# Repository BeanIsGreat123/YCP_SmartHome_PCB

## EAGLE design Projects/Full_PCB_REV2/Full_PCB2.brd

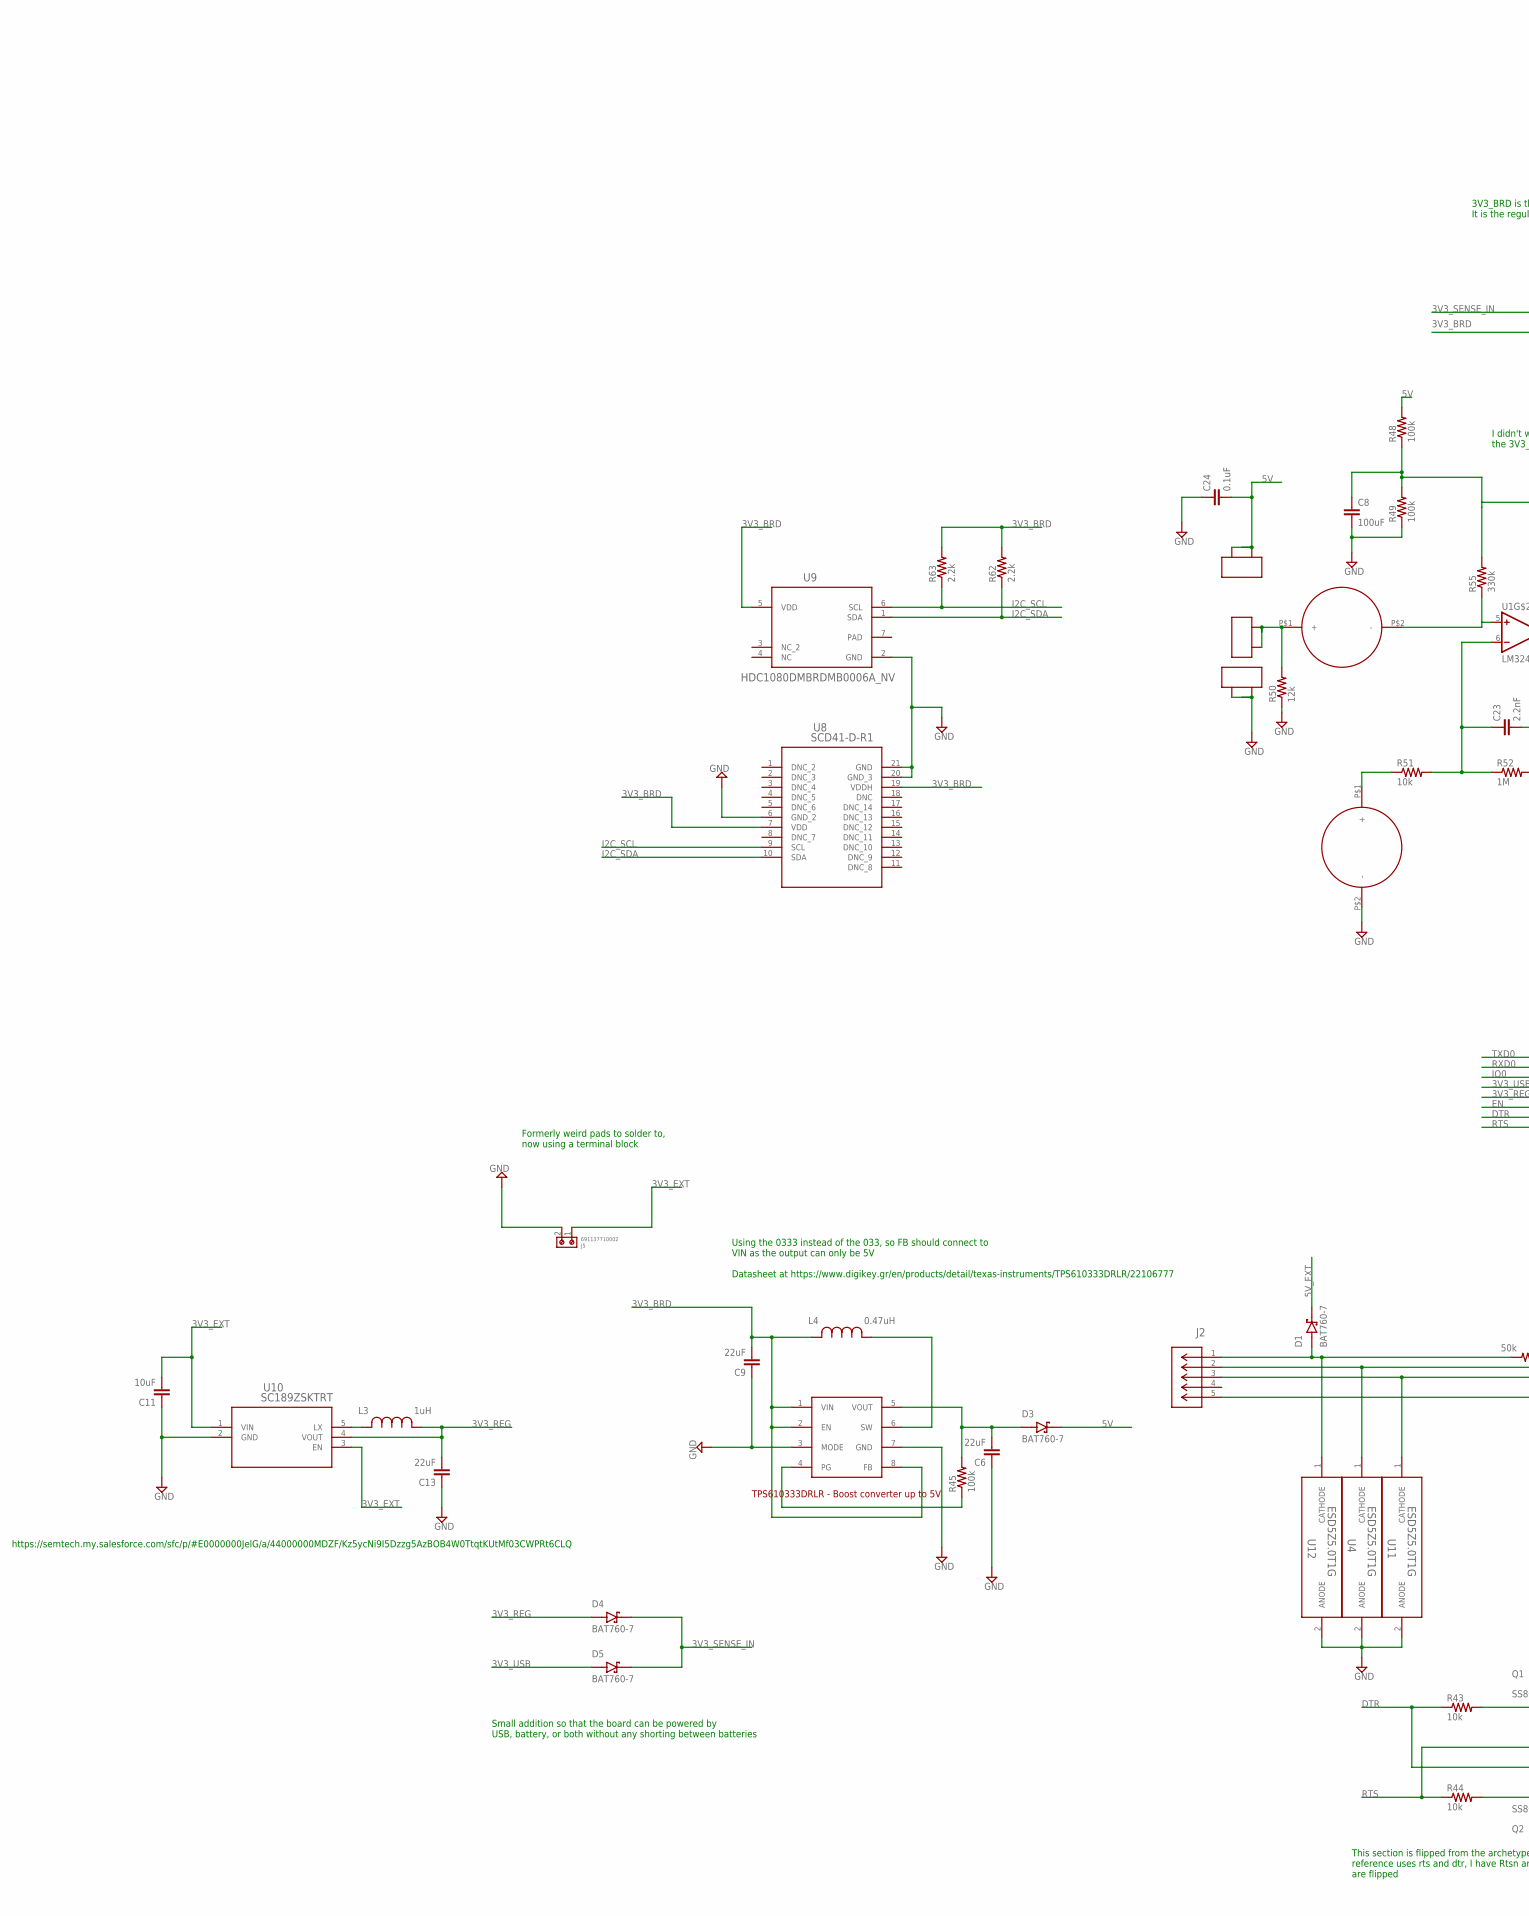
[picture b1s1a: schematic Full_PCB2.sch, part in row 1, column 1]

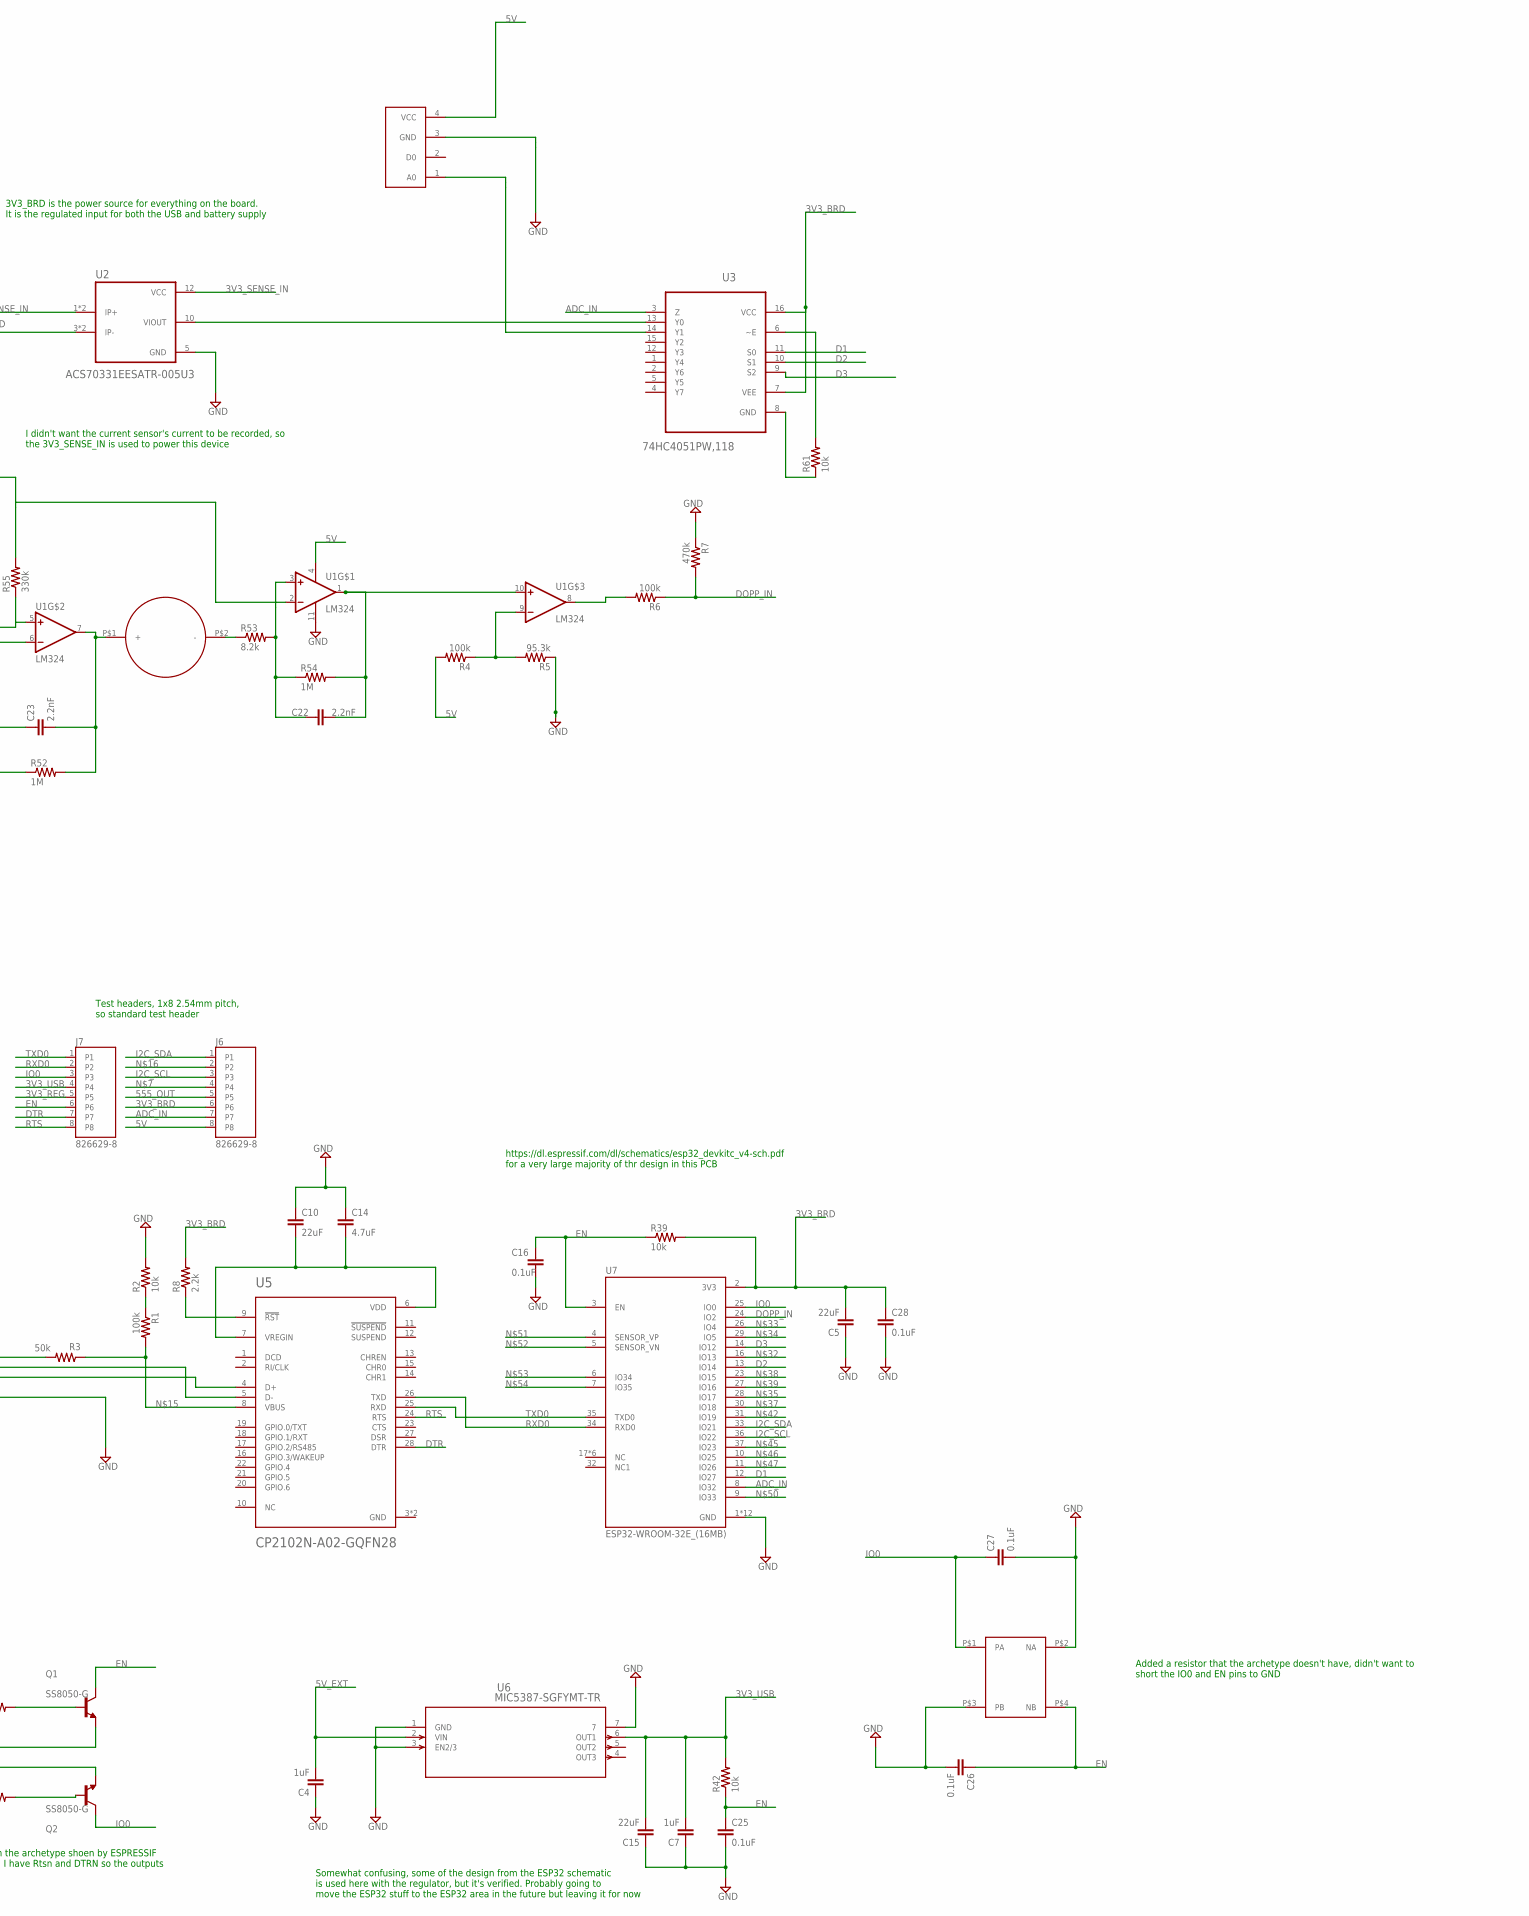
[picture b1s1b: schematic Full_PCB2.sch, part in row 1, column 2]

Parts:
C4, C7: 1uF; C0603
C5, C6, C9, C13, C15: 22uF; C0603
C8: 100uF; C1206
C10: 22uF; C0805
C11: 10uF; C0603
C14: 4.7uF; C0402
C16, C24, C25, C26, C27, C28: 0.1uF; C0402
C22, C23: 2.2nF; C0402
D1, D3, D4, D5: BAT760-7; SOD2513X120N
J2: 10118193-0001LF; CONN_10118193-0001LF_AMP
J5: 691137710002
J6, J7: 826629-8; TE_826629-8
L3: 1uH; DFE252012P-1R0M=P2
L4: 0.47uH; DFE252012P-1R0M=P2
Q1, Q2: SS8050-G; TRANS_SS8050-G
R1, R4, R6, R45, R48, R49: 100k; R0402
R2, R39, R42, R43, R44, R51, R61: 10k; R0402
R3: 50k; R0402
R5: 95.3k; R0402
R7: 470k; R0402
R8, R62, R63: 2.2k; R0402
R50: 12k; R0402
R52, R54: 1M; R0402
R53: 8.2k; R0402
R55: 330k; R0402
U1: LM324; SOIC127P600X175-14N
U2: ACS70331EESATR-005U3; ALLEGRO_ACS70331EESATR-005U3
U3: 74HC4051PW,118; SOP65P640X110-16N
U4, U11, U12: ESD5Z5.0T1G; SOD-523_0P9X1P3_ONS
U5: CP2102N-A02-GQFN28; QFN50P500X500X80-29N
U6: MIC5387-SGFYMT-TR; MLF-6_MT_MCH
U7: ESP32-WROOM-32E_(16MB); XCVR_ESP32-WROOM-32E_(16MB)
U8: SCD41-D-R1; SCD41-D-R1_SEN
U9: HDC1080DMBRDMB0006A_NV; DMB0006A_NV
U10: SC189ZSKTRT; SOT23-5-SC189_SEM
U14: TPS610333DRLR
U$1, U$2, U$5: 2PIN_HEADER
U$3: MQ_7; MQ-7
U$6: 219-2LPST
U$7, U$8, U$9: 865080540002

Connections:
3V3_BRD: C5.2, C9.2, C28.1, J6.6, L4.2, R8.2, R39.2, R62.2, R63.2, U2.3 (IP-), U2.4 (IP-), U3.7 (VEE), U3.16 (VCC), U7.2 (3V3), U8.7 (VDD), U8.19 (VDDH), U9.5 (VDD), U14.1 (VIN), U14.2 (EN), U14.8 (FB)
3V3_EXT: C11.2, J5.1, U10.1 (VIN), U10.3 (EN)
3V3_REG: C13.2, D4.A, J7.5, L3.1, U10.4 (VOUT)
3V3_SENSE_IN: D4.C (K), D5.C (K), U2.1 (IP+), U2.2 (IP+), U2.12 (VCC)
3V3_USB: C7.2, C15.2, D5.A, J7.4, R42.2, U6.6 (OUT1)
5V: C24.2, D3.C (K), J6.8, R4.2, R48.2, U1.4 (VCC+), U$2.1, U$2.2, U$3.4 (VCC)
5V1: C6.2, D3.A, R45.2, U14.5 (VOUT)
5V_EXT: C4.2, D1.C (K), U6.2 (VIN)
555_OUT: J6.5
ADC_IN: J6.7, U3.3 (Z), U7.8 (IO32)
D1: U3.11 (S0), U7.12 (IO27)
D2: U3.10 (S1), U7.13 (IO14)
D3: U3.9 (S2), U7.14 (IO12)
DOPP_IN: R6.1, R7.2, U7.24 (IO2)
DTR: J7.7, Q2.2 (E), R43.1, U5.28 (DTR)
EN: C16.1, C25.1, C26.1, J7.6, Q1.3 (C), R39.1, R42.1, U7.3 (EN), U$6.P$4 (NB)
GND: C4.1, C5.1, C6.1, C7.1, C8.2, C9.1, C10.1, C11.1, C13.1, C14.1, C15.1, C16.2, C24.1, C25.2, C26.2, C27.2, C28.2, J2.5, J5.2, R2.2, R5.1, R7.1, R49.1, R50.1, U1.11 (VCC-), U2.5 (GND), U4.2 (ANODE), U5.3 (GND), U5.29 (GND), U6.1 (GND), U6.3 (EN2/3), U6.7, U7.1 (GND), U7.15 (GND), U7.38 (GND), U7.39_1 (GND), U7.39_2 (GND), U7.39_3 (GND), U7.39_4 (GND), U7.39_5 (GND), U7.39_6 (GND), U7.39_7 (GND), U7.39_8 (GND), U7.39_9 (GND), U8.6 (GND_2), U8.20 (GND_3), U8.21 (GND), U9.2 (GND), U10.2 (GND), U11.2 (ANODE), U12.2 (ANODE), U14.3 (MODE), U14.7 (GND), U$3.3 (GND), U$5.1, U$5.2, U$6.P$2 (NA), U$6.P$3 (PB), U$7.P$2 (-)
I2C_SCL: J6.3, R63.1, U7.36 (IO22), U8.9 (SCL), U9.6 (SCL)
I2C_SDA: J6.1, R62.1, U7.33 (IO21), U8.10 (SDA), U9.1 (SDA)
IO0: C27.1, J7.3, Q2.3 (C), U7.25 (IO0), U$6.P$1 (PA)
unnamed: D1.A, J2.1, R3.2, U12.1 (CATHODE)
unnamed: R4.1, R5.2, U1.9 (INVERTING_INPUT3)
unnamed: C23.1, R51.2, R52.1, U1.6 (INVERTING_INPUT2)
unnamed: C23.2, R52.2, U1.7 (OUTPUT2), U$9.P$1 (+)
unnamed: R53.1, U$9.P$2 (-)
unnamed: C22.1, R53.2, R54.1, U1.3 (NON-INVERTING_INPUT1)
unnamed: J6.4, U2.10 (VIOUT), U3.13 (Y0)
unnamed: R6.2, U1.8 (OUTPUT3)
unnamed: R51.1, U$7.P$1 (+)
unnamed: R45.1, U14.4 (PG)
unnamed: C8.1, R48.1, R49.2, R55.2, U1.2 (INVERTING_INPUT1)
unnamed: J2.2, U4.1 (CATHODE), U5.5 (D-)
unnamed: J2.3, U5.4 (D+), U11.1 (CATHODE)
unnamed: R1.2, R3.1, U5.8 (VBUS)
unnamed: J6.2, U3.14 (Y1), U$3.1 (A0)
unnamed: R1.1, R2.1
unnamed: R8.1, U5.9 (!RST)
unnamed: R61.1, U3.8 (GND)
unnamed: R61.2, U3.6 (~E)
unnamed: C10.2, C14.2, U5.6 (VDD), U5.7 (VREGIN)
unnamed: Q1.1 (B), R43.2
unnamed: Q2.1 (B), R44.2
unnamed: R50.2, U$1.1, U$1.2, U$8.P$1 (+)
unnamed: L3.2, U10.5 (LX)
unnamed: L4.1, U14.6 (SW)
unnamed: R55.1, U1.5 (NON-INVERTING_INPUT2), U$8.P$2 (-)
PAD: U9.7 (PAD)
RTS: J7.8, Q1.2 (E), R44.1, U5.24 (RTS)
RXD0: J7.2, U5.26 (TXD), U7.34 (RXD0)
THRESH_NET: C22.2, R54.2, U1.1 (OUTPUT1), U1.10 (NON-INVERTING_INPUT3)
TXD0: J7.1, U5.25 (RXD), U7.35 (TXD0)

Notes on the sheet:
Small addition so that the board can be powered by USB, battery, or both without any shorting between batteries
3V3_BRD is the power source for everything on the board. It is the regulated input for both the USB and battery supply
Formerly weird pads to solder to, now using a terminal block
Test headers, 1x8 2.54mm pitch, so standard test header
https://dl.espressif.com/dl/schematics/esp32_devkitc_v4-sch.pdf for a very large majority of thr design in this PCB
This section is flipped from the archetype shoen by ESPRESSIF reference uses rts and dtr, I have Rtsn and DTRN so the outputs are flipped
Added a resistor that the archetype doesn't have, didn't want to short the IO0 and EN pins to GND
I didn't want the current sensor's current to be recorded, so the 3V3_SENSE_IN is used to power this device
Using the 0333 instead of the 033, so FB should connect to VIN as the output can only be 5V Datasheet at https://www.digikey.gr/en/products/detail/texas-instruments/TPS610333DRLR/22106777
https://semtech.my.salesforce.com/sfc/p/#E0000000JelG/a/44000000MDZF/Kz5ycNi9I5Dzzg5AzBOB4W0TtqtKUtMf03CWPRt6CLQ
Somewhat confusing, some of the design from the ESP32 schematic is used here with the regulator, but it's verified. Probably going to move the ESP32 stuff to the ESP32 area in the future but leaving it for now

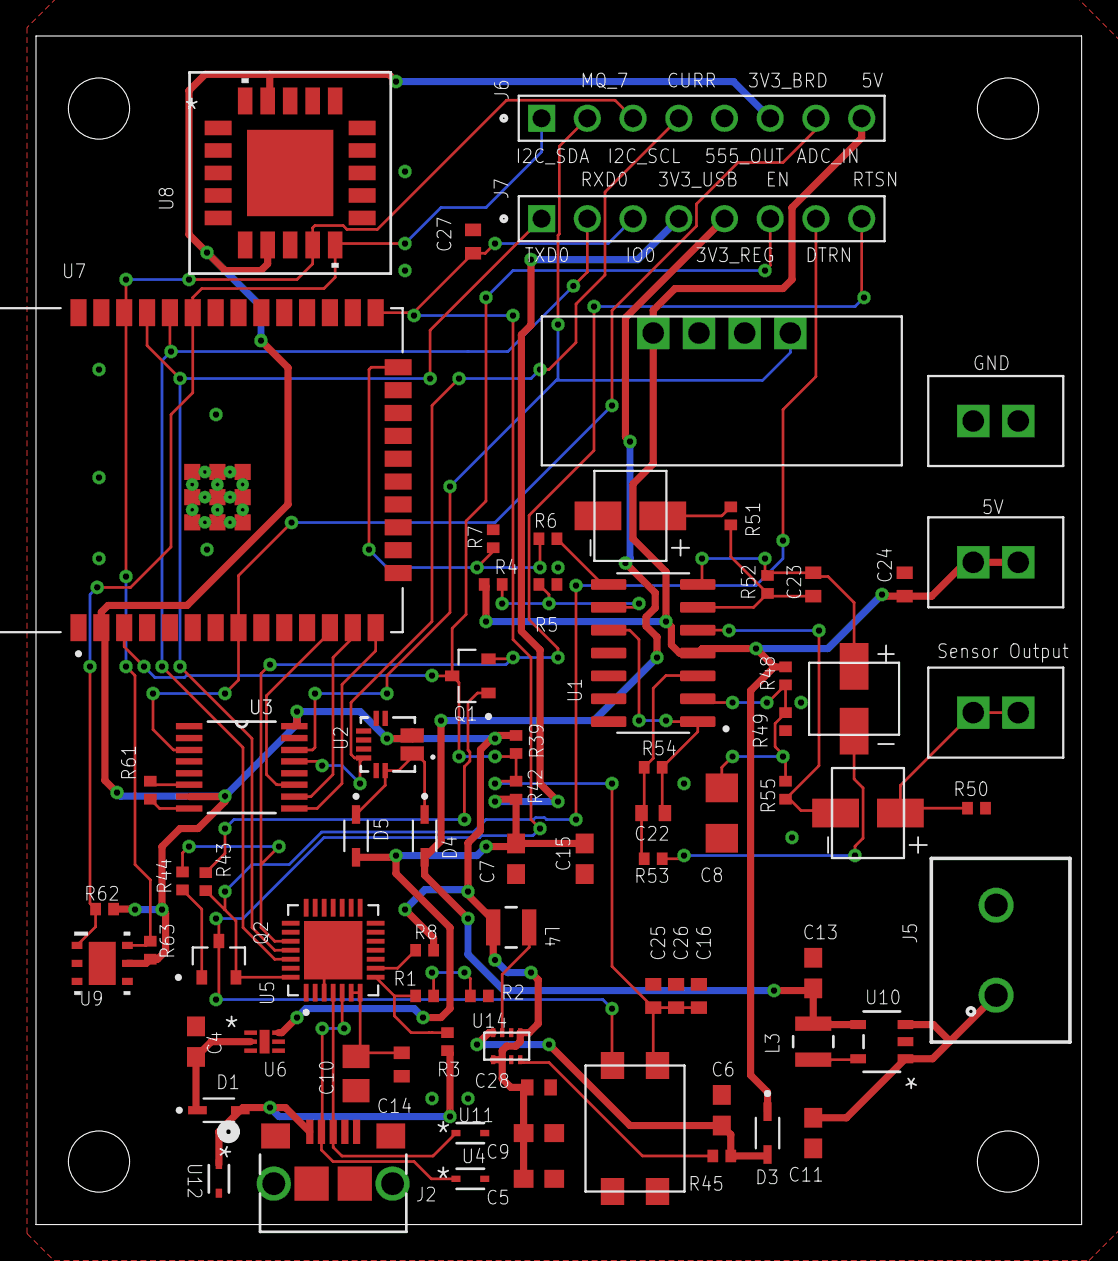
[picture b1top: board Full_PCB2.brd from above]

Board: 2 copper layers, 58.1 x 66.0 mm, 76 parts (0 on the bottom side), 49 nets.

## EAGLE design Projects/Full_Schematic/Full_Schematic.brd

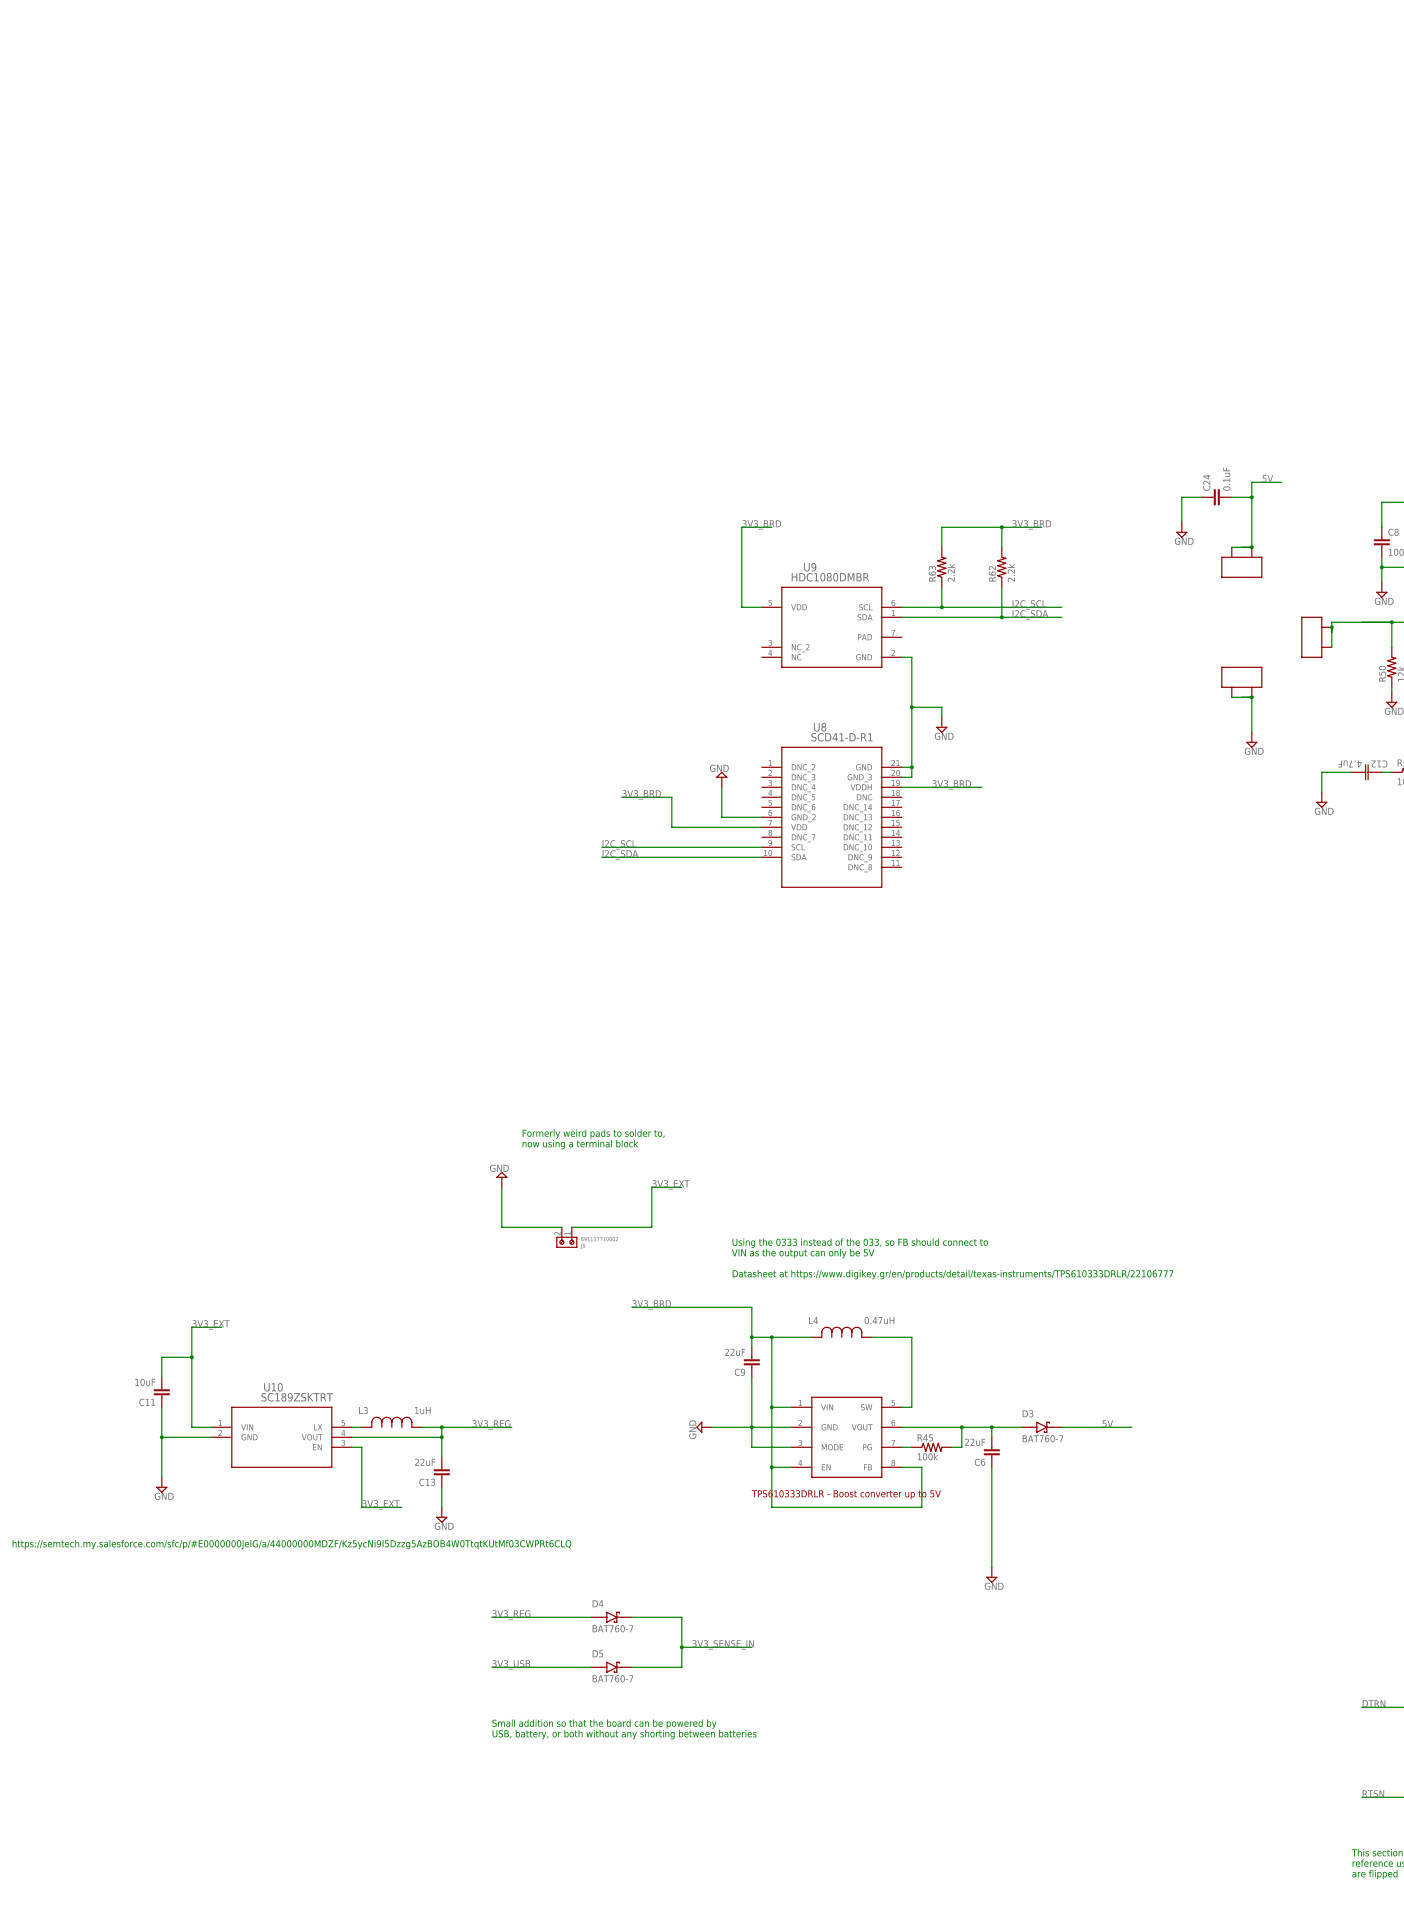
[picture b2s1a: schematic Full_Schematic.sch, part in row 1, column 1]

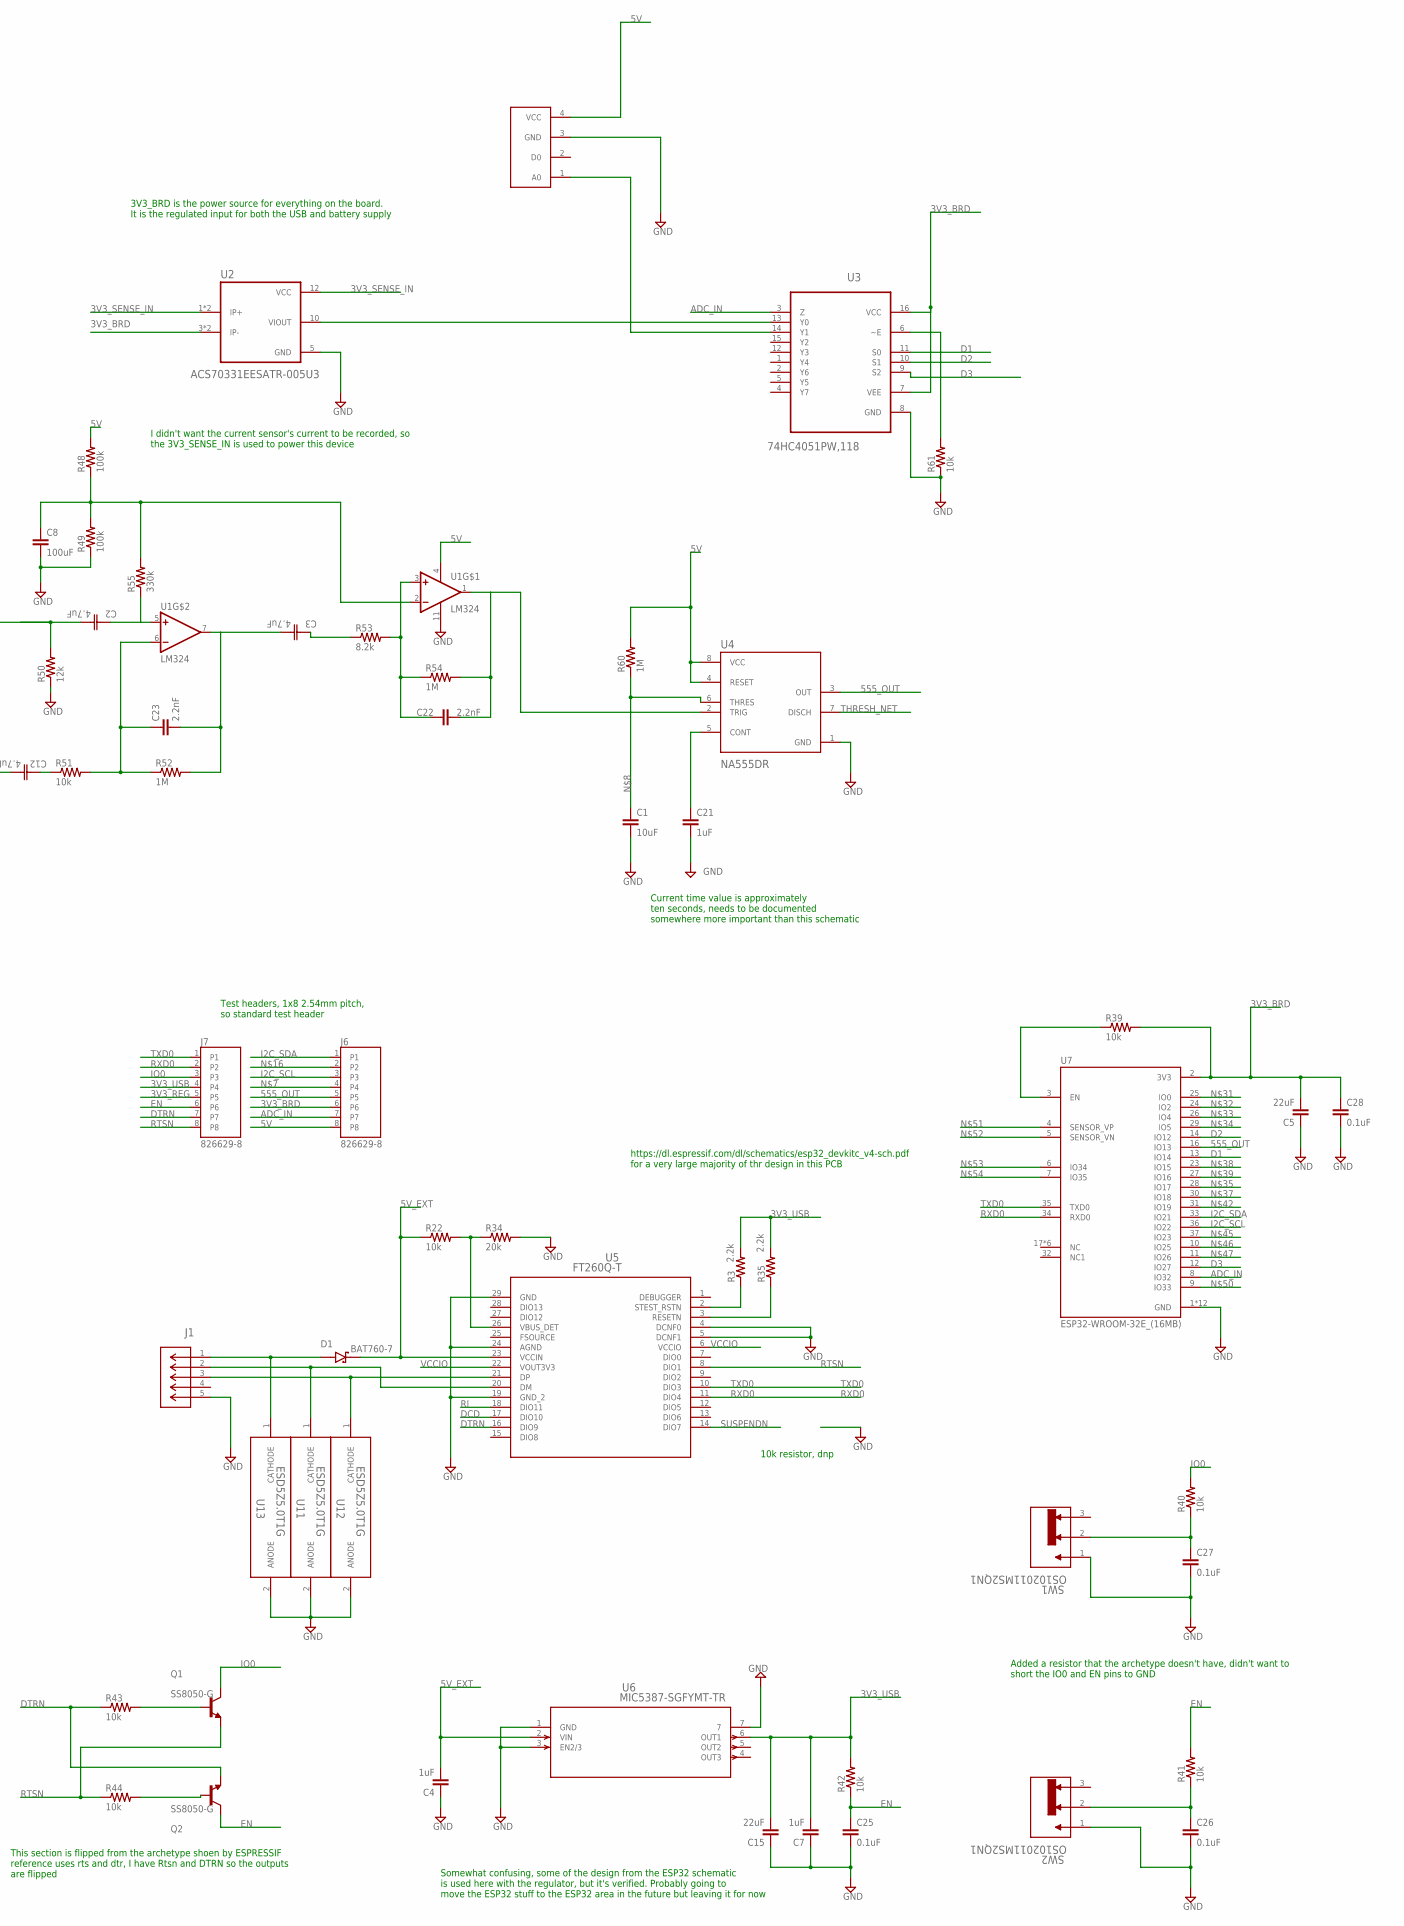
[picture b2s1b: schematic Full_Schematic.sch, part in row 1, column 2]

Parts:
C1, C11: 10uF; C0603
C2, C3, C12: 4.7uF; CAP_WCAP-ATG5_5X11_WRE
C4, C7: 1uF; C0603
C5, C6, C9, C13, C15: 22uF; C0603
C8: 100uF; C1206
C21: 1uF; C0402
C22, C23: 2.2nF; C0402
C24, C25, C26, C27, C28: 0.1uF; C0402
D1, D3, D4, D5: BAT760-7; SOD2513X120N
J1: 10118193-0001LF; CONN_10118193-0001LF_AMP
J5: 691137710002
J6, J7: 826629-8; TE_826629-8
L3: 1uH; DFE252012P-1R0M=P2
L4: 0.47uH; DFE252012P-1R0M=P2
Q1, Q2: SS8050-G; TRANS_SS8050-G
R3, R35, R62, R63: 2.2k; R0402
R22, R39, R40, R41, R42, R43, R44, R51, R61: 10k; R0402
R34: 20k; R0402
R45, R48, R49: 100k; R0402
R50: 12k; R0402
R52, R54, R60: 1M; R0402
R53: 8.2k; R0402
R55: 330k; R0402
SW1, SW2: OS102011MS2QN1; SPDT_OS102011_CNK
U1: LM324; SOIC127P600X175-14N
U2: ACS70331EESATR-005U3; ALLEGRO_ACS70331EESATR-005U3
U3: 74HC4051PW,118; SOP65P640X110-16N
U4: NA555DR; SOIC127P599X175-8N
U5: FT260Q-T; WQFN-28_FTD
U6: MIC5387-SGFYMT-TR; MLF-6_MT_MCH
U7: ESP32-WROOM-32E_(16MB); XCVR_ESP32-WROOM-32E_(16MB)
U8: SCD41-D-R1; SCD41-D-R1_SEN
U9: HDC1080DMBR; DMB0006A
U10: SC189ZSKTRT; SOT23-5-SC189_SEM
U11, U12, U13: ESD5Z5.0T1G; SOD-523_0P9X1P3_ONS
U$1, U$2, U$5: 2PIN_HEADER
U$3: MQ_7; MQ-7
U$4: TPS610333DRLR

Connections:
3V3_BRD: C5.2, C9.2, C28.1, J6.6, L4.2, R39.2, R62.2, R63.2, U2.3 (IP-), U2.4 (IP-), U3.7 (VEE), U3.16 (VCC), U7.2 (3V3), U8.7 (VDD), U8.19 (VDDH), U9.5 (VDD), U$4.1 (VIN), U$4.4 (EN), U$4.8 (FB)
3V3_EXT: C11.2, J5.1, U10.1 (VIN), U10.3 (EN)
3V3_REG: C13.2, D4.A, J7.5, L3.1, U10.4 (VOUT)
3V3_SENSE_IN: D4.C (K), D5.C (K), U2.1 (IP+), U2.2 (IP+), U2.12 (VCC)
3V3_USB: C7.2, C15.2, D5.A, J7.4, R3.2, R35.2, R42.2, U6.6 (OUT1)
5V: C24.2, D3.C (K), J6.8, R48.2, R60.2, U1.4 (VCC+), U4.4 (RESET), U4.8 (VCC), U$2.1, U$2.2, U$3.4 (VCC)
5V1: C6.2, D3.A, R45.2, U$4.6 (VOUT)
5V_EXT: C4.2, D1.C (K), R22.1, U5.23 (VCCIN), U6.2 (VIN)
555_OUT: J6.5, U4.3 (OUT), U7.16 (IO13)
ADC_IN: J6.7, U3.3 (Z), U7.8 (IO32)
D1: U3.11 (S0), U7.13 (IO14)
D2: U3.10 (S1), U7.14 (IO12)
D3: U3.9 (S2), U7.12 (IO27)
DCD: U5.17 (DIO10)
DTRN: J7.7, Q2.2 (E), R43.1, U5.16 (DIO9)
EN: C25.1, J7.6, Q2.3 (C), R41.2, R42.1
FSOURCE: U5.25 (FSOURCE)
GND: C1.2, C4.1, C5.1, C6.1, C7.1, C8.2, C9.1, C11.1, C12.2, C13.1, C15.1, C21.2, C24.1, C25.2, C26.2, C27.2, C28.2, J1.5, J5.2, R34.2, R49.1, R50.1, R61.1, SW1.1, SW2.1, U1.11 (VCC-), U2.5 (GND), U3.8 (GND), U4.1 (GND), U5.4 (DCNF0), U5.5 (DCNF1), U5.19 (GND_2), U5.24 (AGND), U5.29 (GND), U6.1 (GND), U6.3 (EN2/3), U6.7, U7.1 (GND), U7.15 (GND), U7.38 (GND), U7.39_1 (GND), U7.39_2 (GND), U7.39_3 (GND), U7.39_4 (GND), U7.39_5 (GND), U7.39_6 (GND), U7.39_7 (GND), U7.39_8 (GND), U7.39_9 (GND), U8.6 (GND_2), U8.20 (GND_3), U8.21 (GND), U9.2 (GND), U10.2 (GND), U11.2 (ANODE), U12.2 (ANODE), U13.2 (ANODE), U$3.3 (GND), U$4.2 (GND), U$4.3 (MODE), U$5.1, U$5.2
I2C_SCL: J6.3, R63.1, U7.36 (IO22), U8.9 (SCL), U9.6 (SCL)
I2C_SDA: J6.1, R62.1, U7.33 (IO21), U8.10 (SDA), U9.1 (SDA)
IO0: J7.3, Q1.3 (C), R40.2
unnamed: C26.1, R41.1, SW2.2
unnamed: C23.1, R51.2, R52.1, U1.6 (INVERTING_INPUT2)
unnamed: C3.2, C23.2, R52.2, U1.7 (OUTPUT2)
unnamed: C3.1, R53.1
unnamed: C22.1, R53.2, R54.1, U1.3 (NON-INVERTING_INPUT1)
unnamed: J6.4, U2.10 (VIOUT), U3.13 (Y0)
unnamed: C1.1, R60.1, U4.6 (THRES)
unnamed: C8.1, R48.1, R49.2, R55.2, U1.2 (INVERTING_INPUT1)
unnamed: C27.1, R40.1, SW1.2
unnamed: C12.1, R51.1
unnamed: J6.2, U3.14 (Y1), U$3.1 (A0)
unnamed: C21.1, U4.5 (CONT)
unnamed: D1.A, J1.1, U13.1 (CATHODE)
unnamed: R61.2, U3.6 (~E)
unnamed: J1.2, U5.20 (DM), U11.1 (CATHODE)
unnamed: J1.3, U5.21 (DP), U12.1 (CATHODE)
unnamed: Q1.1 (B), R43.2
unnamed: Q2.1 (B), R44.2
unnamed: R35.1, U5.3 (RESETN)
unnamed: R22.2, R34.1, U5.26 (VBUS_DET)
unnamed: R39.1, U7.3 (EN)
unnamed: C2.2, R50.2, U$1.1, U$1.2
unnamed: R3.1, U5.2 (STEST_RSTN)
unnamed: L3.2, U10.5 (LX)
unnamed: L4.1, U$4.5 (SW)
unnamed: R45.1, U$4.7 (PG)
unnamed: C2.1, R55.1, U1.5 (NON-INVERTING_INPUT2)
PAD: U9.7 (PAD)
RI: U5.18 (DIO11)
RTSN: J7.8, Q1.2 (E), R44.1, U5.8 (DIO1)
RXD0: J7.2, U5.11 (DIO4), U7.34 (RXD0)
SUSPENDN: U5.14 (DIO7)
THRESH_NET: C22.2, R54.2, U1.1 (OUTPUT1), U4.2 (TRIG), U4.7 (DISCH)
TXD0: J7.1, U5.10 (DIO3), U7.35 (TXD0)
VCCIO: U5.6 (VCCIO), U5.22 (VOUT3V3)

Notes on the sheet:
Current time value is approximately ten seconds, needs to be documented somewhere more important than this schematic
Small addition so that the board can be powered by USB, battery, or both without any shorting between batteries
3V3_BRD is the power source for everything on the board. It is the regulated input for both the USB and battery supply
Formerly weird pads to solder to, now using a terminal block
Test headers, 1x8 2.54mm pitch, so standard test header
10k resistor, dnp
https://dl.espressif.com/dl/schematics/esp32_devkitc_v4-sch.pdf for a very large majority of thr design in this PCB
This section is flipped from the archetype shoen by ESPRESSIF reference uses rts and dtr, I have Rtsn and DTRN so the outputs are flipped
Added a resistor that the archetype doesn't have, didn't want to short the IO0 and EN pins to GND
I didn't want the current sensor's current to be recorded, so the 3V3_SENSE_IN is used to power this device
Using the 0333 instead of the 033, so FB should connect to VIN as the output can only be 5V Datasheet at https://www.digikey.gr/en/products/detail/texas-instruments/TPS610333DRLR/22106777
https://semtech.my.salesforce.com/sfc/p/#E0000000JelG/a/44000000MDZF/Kz5ycNi9I5Dzzg5AzBOB4W0TtqtKUtMf03CWPRt6CLQ
Somewhat confusing, some of the design from the ESP32 schematic is used here with the regulator, but it's verified. Probably going to move the ESP32 stuff to the ESP32 area in the future but leaving it for now

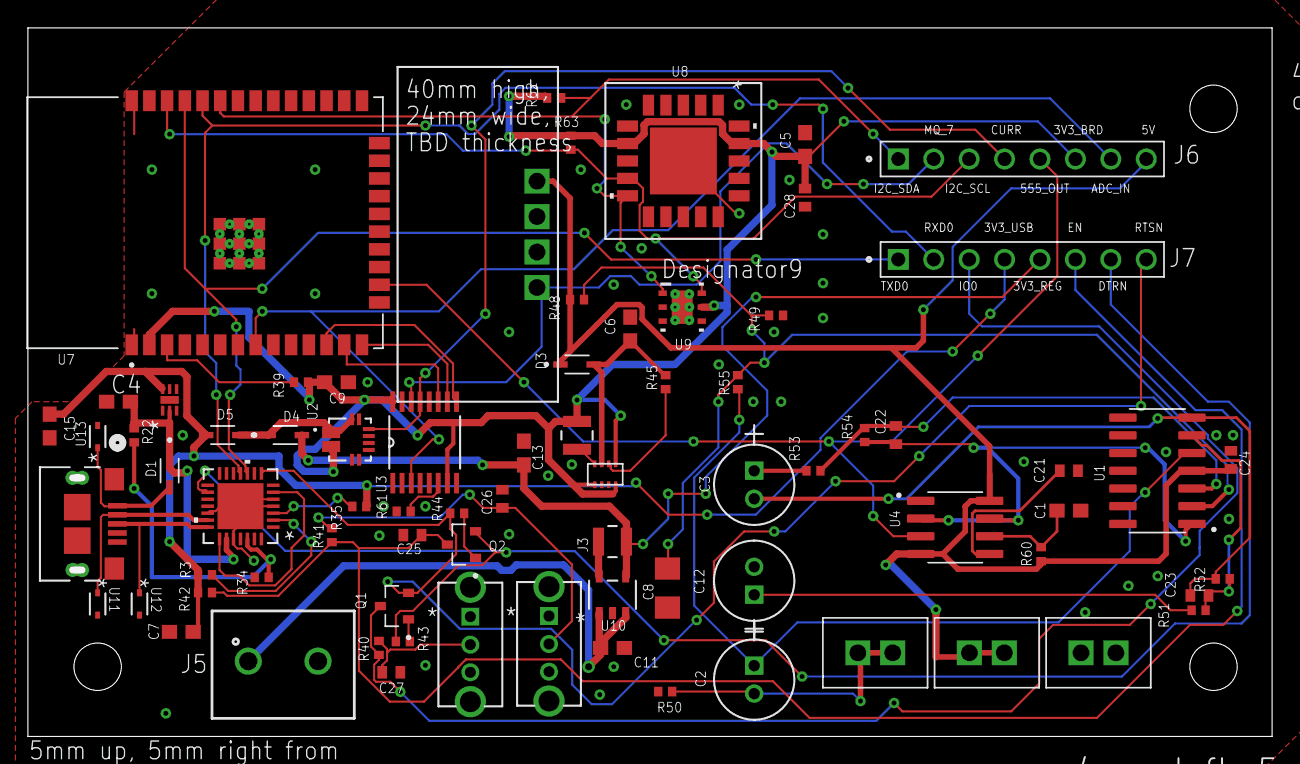
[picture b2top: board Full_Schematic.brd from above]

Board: 2 copper layers, 88.7 x 50.3 mm, 76 parts (0 on the bottom side), 51 nets.

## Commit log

2024-02-28 Project, components, and schematic added
    Pushing the entire project up to now
2024-02-28 Project and Schematics added
    All projects and schematics
2024-03-02 Old ESP8266 configuration has been veto'd, now going with the esp32 for this design. Will hopefully update to the 8266(or a similar cheaper microprocessor) in the future.
2024-03-02 Most recent batch of new components
2024-03-02 Updated version of Analog_Input schematic
2024-03-02 Commit 3/1/2024
2024-03-02 Updated Schematics
2024-03-03 I hadn't realized that you cannot put multiple schematics into one pcb, so full schematic is just a copy-paste version of all of the other schematics. Full_Schematic.sch is also the only schematic to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
2024-03-03 I'm tired boss
2024-03-18 Final revision of the Full Schematic, haven't updated in a while since I was soloing this one.
2024-04-12 Second revision of PCB
2024-04-16 Add files via upload
    Unfinished revision of the PCB firmware
2024-04-18 I2C Timing Implemented
2024-04-20 Motion timing and I2C comms. implemented
2024-04-20 Newest revision
    No mux, current sensor, or communication (ESPNOW)

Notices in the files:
parts and their libraries:
COPYRIGHT: Copyright (C) 2024 Ultra Librarian. All rights reserved.
